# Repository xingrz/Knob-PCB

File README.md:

Knob-PCB
==========

Knob 是一个蓝牙遥控器，基于 [ESP32-C3](https://www.espressif.com/zh-hans/products/socs/esp32-c3) 平台开发。

观看视频: https://www.bilibili.com/video/BV1Nq4y1Z7mp

## 主要元器件

* 主控: 乐鑫 ESP32-C3-MINI-1 (常温版 ESP32-C3FN4)
* 编码器: BOURNS PEC11R-4015F-S0024

## EDA

[KiCad](https://kicad.org/) 5.1.9

## 生产

仓库中的 Gerber、BOM、POS 可直接提交到[嘉立创](https://www.jlc.com/)打样 PCB 和贴片。[BOM 表](KNOB_MAIN_BOM.csv)中包含了嘉立创的原件编号，可自动精确匹配。

## 软件

详见 [Knob-FW](https://github.com/Knob-FW)

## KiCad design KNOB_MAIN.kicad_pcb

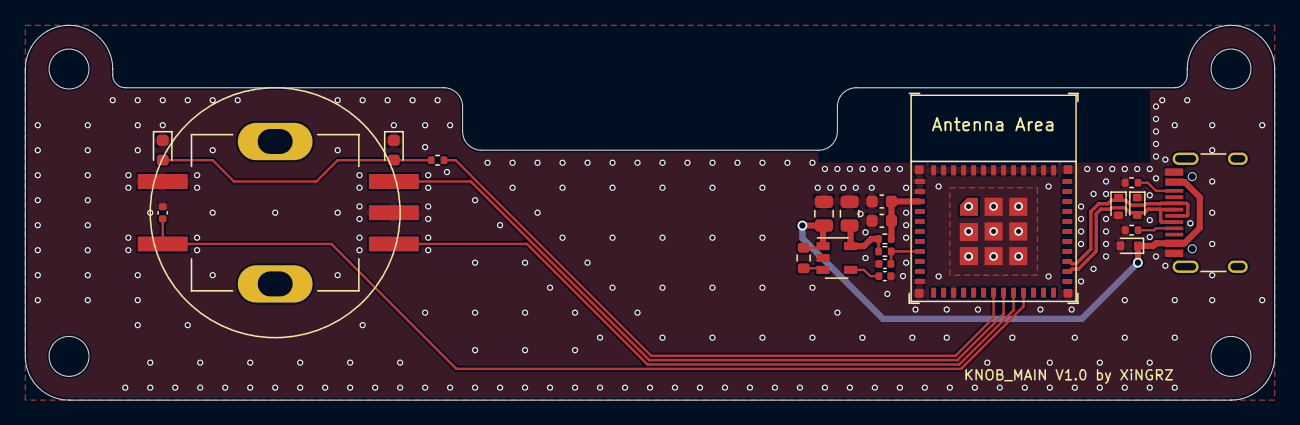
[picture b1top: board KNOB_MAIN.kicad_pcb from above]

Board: 2 copper layers, 100.0 x 30.0 mm, 26 parts (0 on the bottom side), 16 nets.

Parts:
C1, C2: 10uF/25V; C_0805_2012Metric
C3: 1uF/25V; C_0402_1005Metric
C4: 10uF/10V; C_0603_1608Metric
C5: 100nF/50V; C_0603_1608Metric
C6: 10nF; C_0402_1005Metric
C7: 100nF; C_0402_1005Metric
D1, D2, D3: LESD5Z5.0CT1G; D_SOD-523
D4, D5: BLUE; LED_0603_1608Metric
H1, H2, H3, H4: Mount; MountingHole_3.2mm_M3
J1: HRO_TYPE-C-31-M-12
R1, R2: 5.1K; R_0402_1005Metric
R3: 10K; R_0402_1005Metric
R4: 0; R_0402_1005Metric
R5: 0; R_0603_1608Metric
R6: 220; R_0402_1005Metric
SW1: PEC11R-4220F-S0024; BOURNS_PEC11R-4XXXX-SXXXX_SMD
U1: LP2992AIM5X-3.3; SOT-23-5
U2: ESP32-C3-MINI-1

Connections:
+3V3: C2.1, R3.1, R4.1, U1.5
+5V: C1.1, D3.1, J1.A4, J1.A9, J1.B4, J1.B9, R5.2, U1.1
/D+: D1.1, J1.A6, J1.B6, U2.27
/D-: D2.2, J1.A7, J1.B7, U2.26
/ENTER: C7.1, SW1.S1, U2.21
/ROTARY_A: SW1.A, U2.20
/ROTARY_B: SW1.B, U2.19
/STATUS: R6.2, U2.18
GND: C1.2, C2.2, C3.2, C4.2, C5.2, C6.2, C7.2, D1.2, D2.1, D3.2, D4.1, D5.1, J1.A1, J1.A12, J1.B1, J1.B12, R1.1, R2.1, SW1.C, SW1.S2, U1.2, U2.1, U2.2, U2.11, U2.14, U2.36
unnamed: C3.1, R3.2, U2.8
unnamed: C4.1, C5.1, R4.2, U2.3
unnamed: C6.1, U1.4
unnamed: D4.2, D5.2, R6.1
unnamed: J1.A5, R1.2
unnamed: J1.B5, R2.2
unnamed: R5.1, U1.3

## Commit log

2021-08-22 Init repository
2021-08-23 Output gerber
2021-08-23 Main sch and pcb layout
2021-08-23 Add front panel
2021-08-23 Change to M3 screws
2021-08-23 Update packages
2021-08-31 Use LP2992AIM5X-3.3 LDO and adjust layout
2021-09-01 Use 1.6mm board for better strength
2021-09-01 Increase radius of knob hole to 10.4mm
2021-09-01 Add specific custom number on panel
2021-09-13 Add 100nF debounce capacitor to push pin
2021-10-01 Correct model number of encoder
2021-10-01 Add README
2021-10-01 Update documents
